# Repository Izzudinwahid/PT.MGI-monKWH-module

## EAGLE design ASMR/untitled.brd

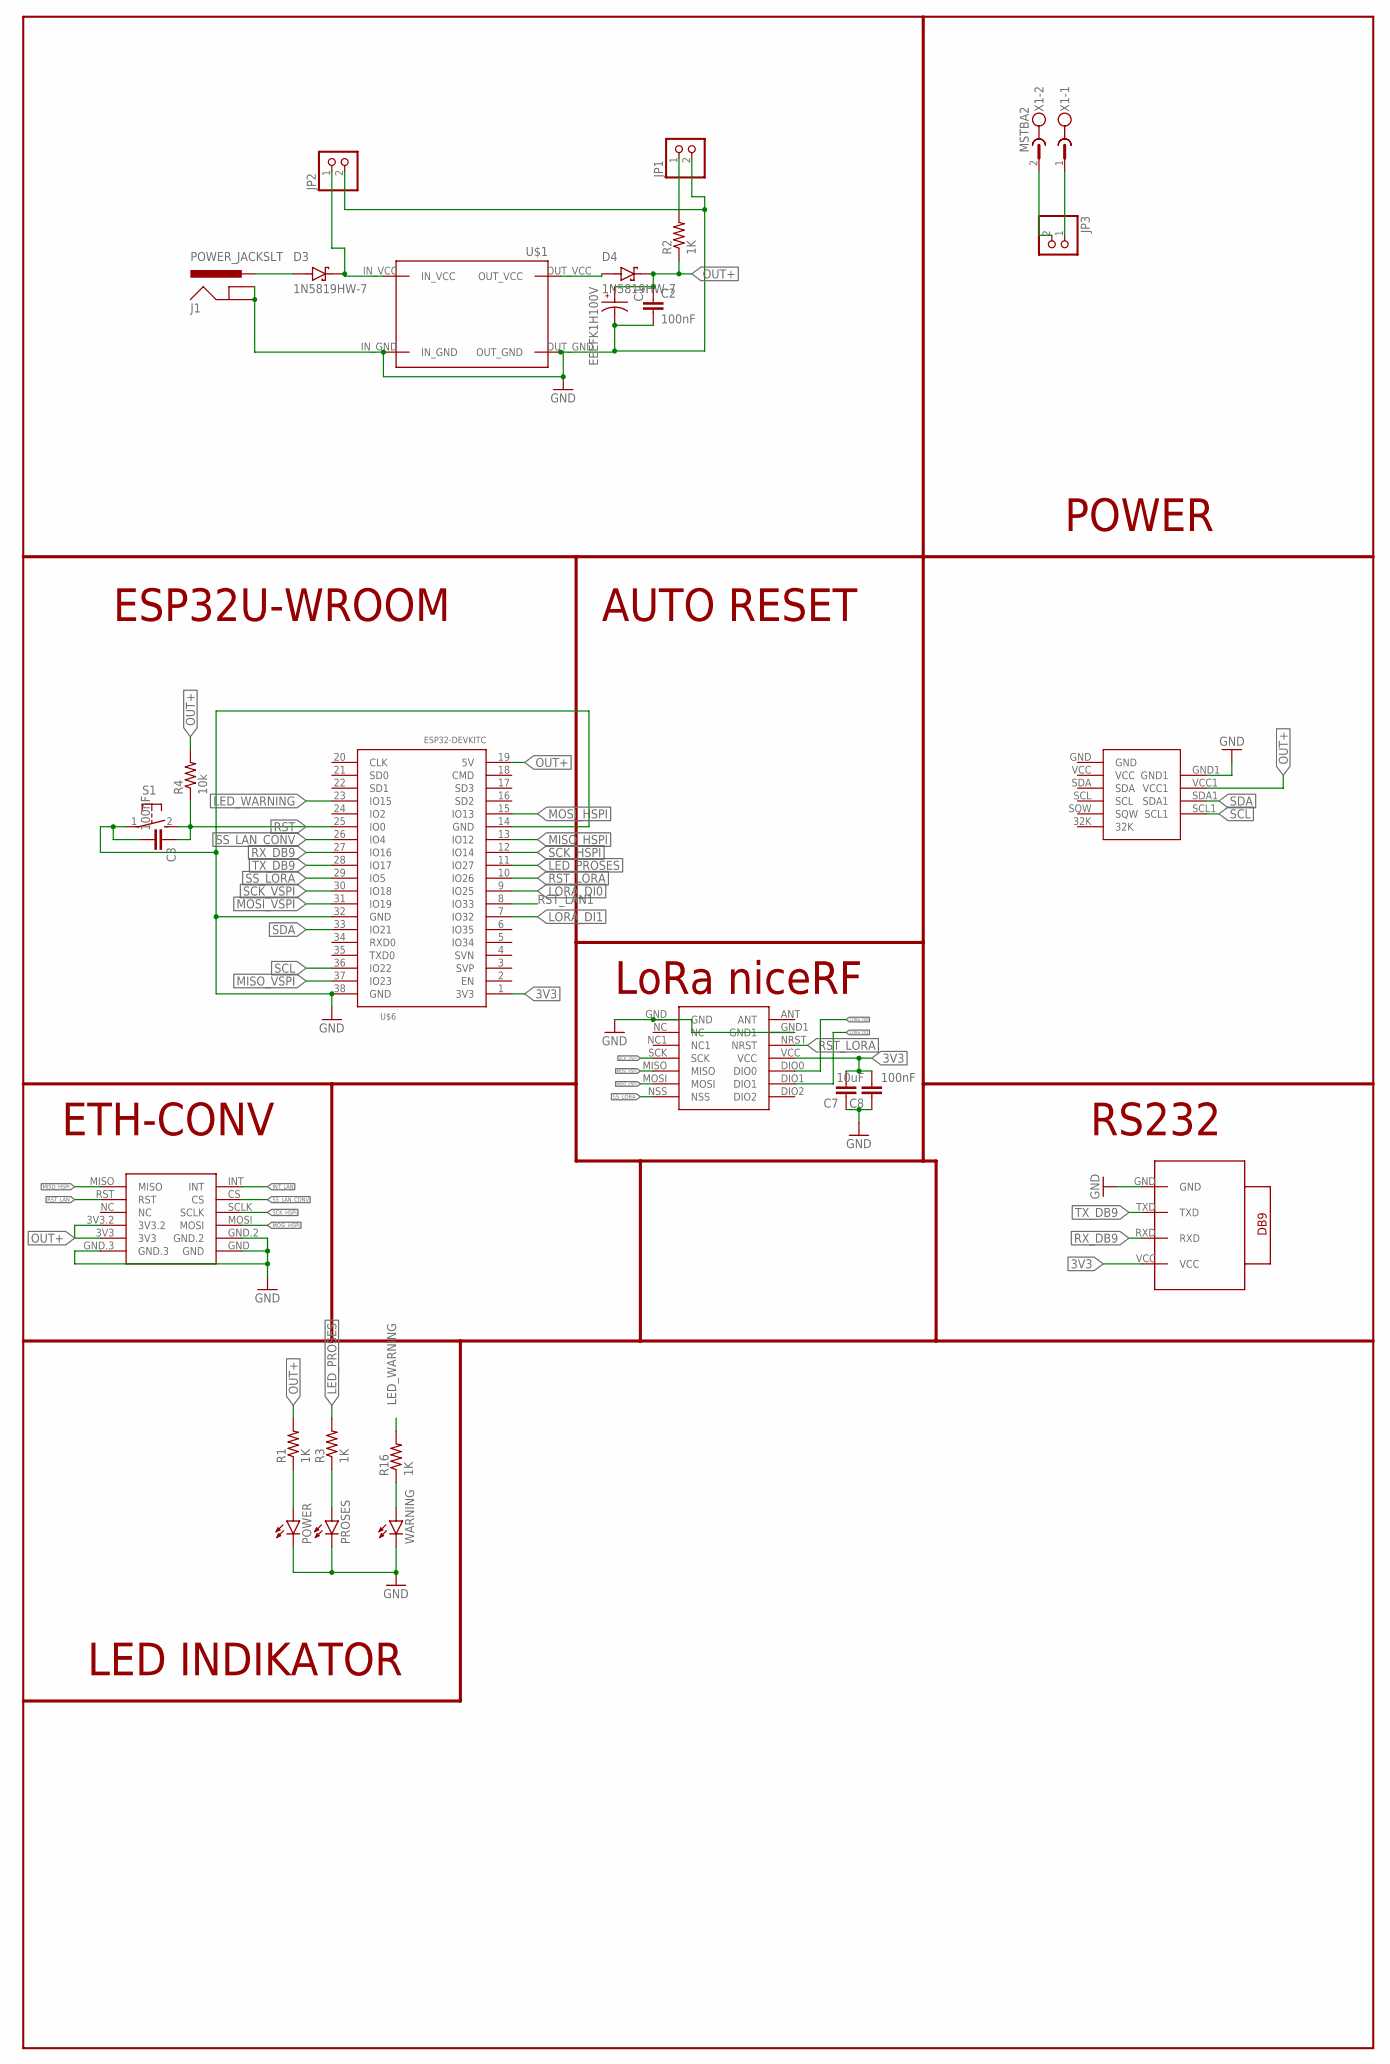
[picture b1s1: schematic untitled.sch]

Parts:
C1: EEEFK1H100V; CAP_EEEFK1H100V
C2, C3, C8: 100nF; C0805K
C7: 10uF; C0805K
D3, D4: 1N5819HW-7; SOD3715X145N
J1: POWER_JACKSLT; POWER_JACK_SLOT
JP1, JP2, JP3: PINHD-1X2; 1X02
LORA-NICERF-V1: LORA-NICERF-V2
POWER: TLLR4400; LED3MM
PROSES: TLLR4400; LED3MM
R1, R2, R3, R16: 1K; M0805
R4: 10k; M0805
RTC1: RTC3231
S1: 31-XX; B3F-31XX
U$1: STEPDOWN_SY8205
U$3: MINI_W5500
U$5: RS232-BREAKOUTBREAKOUT; RS232-BREAKOUT
U$6: ESP32DEVKITC; ESP32-DEVKITC
WARNING: TLLR4400; LED3MM
X1: MSTBA2

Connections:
3V3: C7.2, C8.2, LORA-NICERF-V1.VCC, U$5.VCC, U$6.1 (3V3)
GND: C1.2, C2.2, C3.2, C7.1, C8.1, J1.GND@1 (GNDBREAK), J1.GND@2 (GND), JP1.2, JP2.2, LORA-NICERF-V1.GND, LORA-NICERF-V1.GND1, POWER.K (C), PROSES.K (C), RTC1.GND1, S1.1, U$1.IN_GND, U$1.OUT_GND, U$3.GND, U$3.GND.2, U$3.GND.3, U$5.GND, U$6.14 (GND), U$6.32 (GND), U$6.38 (GND), WARNING.K (C)
INT_LAN: U$3.INT
LED_PROSES: R3.2, U$6.11 (IO27)
LED_WARNING: R16.2, U$6.23 (IO15)
LORA_DI0: LORA-NICERF-V1.DIO0, U$6.9 (IO25)
LORA_DI1: LORA-NICERF-V1.DIO1, U$6.7 (IO32)
MISO_HSPI: U$3.MISO, U$6.13 (IO12)
MISO_VSPI: LORA-NICERF-V1.MOSI, U$6.37 (IO23)
MOSI_HSPI: U$3.MOSI, U$6.15 (IO13)
MOSI_VSPI: LORA-NICERF-V1.MISO, U$6.31 (IO19)
unnamed: POWER.A, R1.1
unnamed: D3.A, J1.PWR
unnamed: PROSES.A, R3.1
unnamed: D3.C (K), JP2.1, U$1.IN_VCC
unnamed: JP3.2, X1.2
unnamed: D4.A, U$1.OUT_VCC
unnamed: JP1.1, R2.2
unnamed: JP3.1, X1.1
unnamed: R16.1, WARNING.A
OUT+: C1.1, C2.1, D4.C (K), R1.2, R2.1, R4.2, RTC1.VCC1, U$3.3V3, U$3.3V3.2, U$6.19 (5V)
RST: C3.1, R4.1, S1.2 (S), U$6.25 (IO0)
RST_LAN: U$3.RST
RST_LAN1: U$6.8 (IO33)
RST_LORA: LORA-NICERF-V1.NRST, U$6.10 (IO26)
RX_DB9: U$5.RXD, U$6.27 (IO16)
SCK_HSPI: U$3.SCLK, U$6.12 (IO14)
SCK_VSPI: LORA-NICERF-V1.SCK, U$6.30 (IO18)
SCL: RTC1.SCL1, U$6.36 (IO22)
SDA: RTC1.SDA1, U$6.33 (IO21)
SS_LAN_CONV: U$3.CS, U$6.26 (IO4)
SS_LORA: LORA-NICERF-V1.NSS, U$6.29 (IO5)
TX_DB9: U$5.TXD, U$6.28 (IO17)

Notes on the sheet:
POWER
ESP32U-WROOM
AUTO RESET
LoRa niceRF
ETH-CONV
RS232
LED INDIKATOR

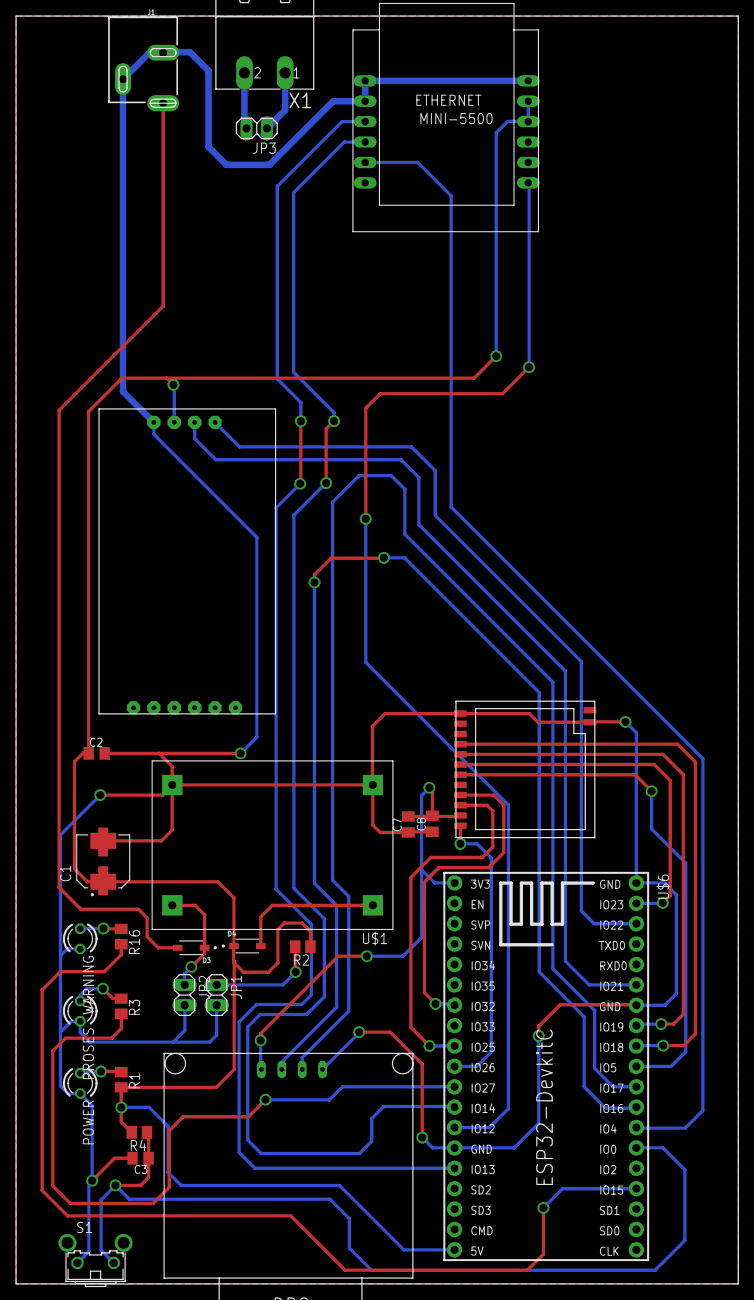
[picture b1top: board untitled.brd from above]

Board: 2 copper layers, 90.0 x 158.0 mm, 27 parts (0 on the bottom side), 30 nets.

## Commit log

2022-08-22 PCb monKWH-prototype
2022-08-22 revisi PCB
2022-08-22 pembuatan file .brd

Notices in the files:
parts and their libraries:
SparkFun-Connectors: Licensing: Creative Commons ShareAlike 4.0 International - https://creativecommons.org/licenses/by-sa/4.0
